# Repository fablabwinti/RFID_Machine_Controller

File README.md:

# RFID_Machine_Controller
This repository contains the hardware design files (eagle) and the firmware (Arduino) for the Fablab Winti RFID machine access controller. 
## Hardware features
- Based on ESP8266 so it has direct access to WiFi
- RFID reader 
- OLED display
- Piezo buzzer
- Multi-color LED
- SD card for event logging
- RTC for accurate time keeping without network access
- Isolated output with screw terminal
  - Option 1: Relay output: 250V, 5A, NC or NO with a 5x20mm fuse
  - Option 2: Opto-coupled output (50V, 40mA)
- Input voltage: 5V ±0.5V with input protection (reverse voltage protection, overvoltage protection)
- Three input connecters: 5.5x2.1mm DC jack, Micro USB jack, screw termianl

## Firmware features
- Easy web based configuration
- Time sync through NTP
- Automatic synchronization of local RTC 
- Automatic update of user database from server
- Local storage of access rights: works during network failures
- Local data logging to SD-Card or Flash (TBD)
- Transmit log data to server as soon as it is available

## Arduino IDE
### Add Board to IDE
File -> Preferences -> Settings -> Additional boards manager URLs: http://arduino.esp8266.com/stable/package_esp8266com_index.json  
### Install Board
Tools -> Boards -> Boards Manager
Search for "esp8266" and install it
### Select Board
Tools -> Boards -> esp8622 -> "Generic ESP8622 Module"
### Board Configurations
Select the following settings under "Tools"

### Install Libraries
Unzip "FabLabRFID_Library.zip" in the arduino library folder:

- Windows: `C:\Users\{username}\Documents\Arduino`
- macOS: `/Users/{username}/Documents/Arduino`
- Linux: `/home/{username}/Arduino`

#### Manually

Tools -> Manage Libraries

Install all libraries as described in Fablab_RFID_control.ino, line 52 to 70 (?)

MRFC522: Download from git (https://github.com/miguelbalboa/rfid) and add it to the library (.../Documents/Arduino/Libraries/...)

## Upload Flash Content

The `spiffs_flash.py` script automatically builds the SPIFFS filesystem image from the `data` directory and uploads it to the ESP8266.

### Prerequisites
- Python 3.x installed
- ESP8266 connected via USB
- Arduino15 directory present (auto-detected or manually specified)

### Usage

Basic upload (auto-detects Arduino15 directory):
```bash
python spiffs_flash.py --port COM8
```

With custom options:
```bash
# Specify Arduino15 directory manually
python spiffs_flash.py --port COM8 --arduino-root "C:\Users\YourName\AppData\Local\Arduino15"

# Erase SPIFFS region before writing (if write fails)
python spiffs_flash.py --port COM8 --erase-region

# Keep temporary build files for inspection
python spiffs_flash.py --port COM8 --keep-temp

# Use existing .bin file (skip build)
python spiffs_flash.py --port COM8 --bin path\to\existing.spiffs.bin
```

### Troubleshooting
- If Arduino15 not found, the script will prompt for the path
- Use `--erase-region` if you encounter write errors (preserves main firmware)
- Change COM port number to match your device (check Device Manager on Windows)

# License
-Firmware under GNU LGPL Version 3
-Hardware under Creative Commons 4.0 license: CC-BY-SA

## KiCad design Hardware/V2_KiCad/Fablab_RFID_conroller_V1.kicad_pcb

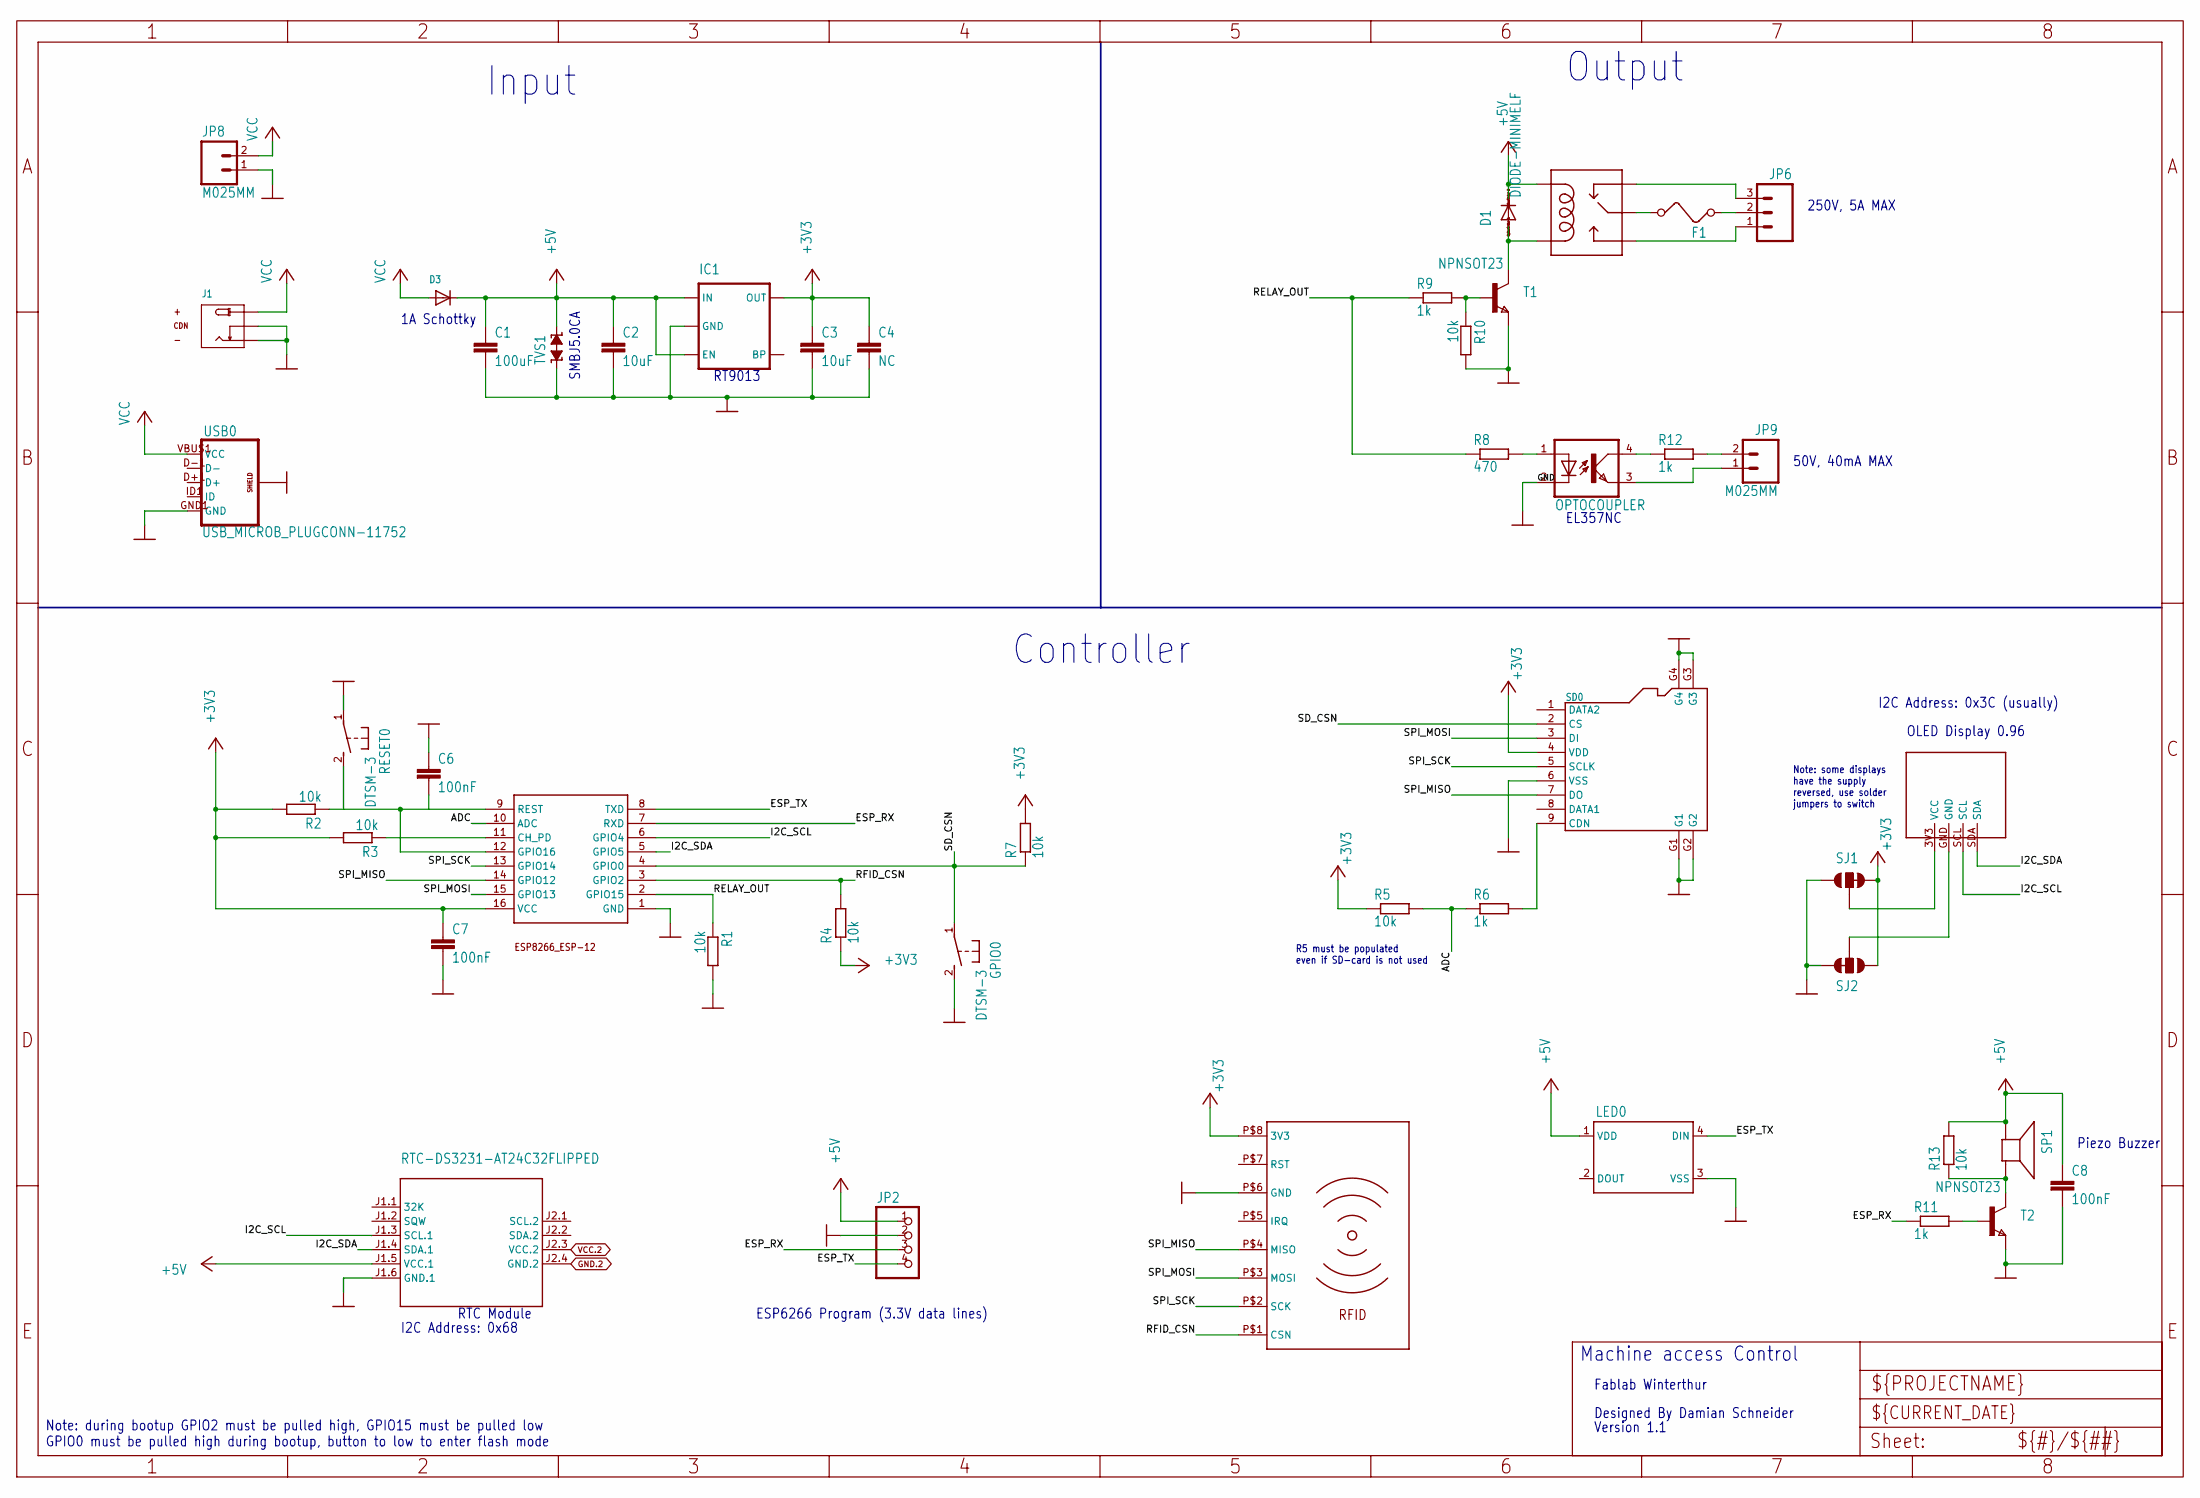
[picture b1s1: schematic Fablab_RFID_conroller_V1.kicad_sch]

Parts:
C1: 100uF; C1206
C2, C3: 10uF; C0805
C4: NC; C1206
C6, C7, C8: 100nF; C0603
D1: DIODE-MINIMELF; MINIMELF
D3: DIODESMA; SMADIODE
ESP0: ESP8266_ESP-12; ESP8266-ESP12
F1: FUSE
GPIO0: DTSM-3
IC1: V_REG_LDOSMD; SOT23-5
J1: JACK-DC-3P-3410020P1; PW-3P-2.1
JP2: HEADER-1X476MIL; 1X04_ROUND_76
JP6: M03-SCREW-5MM; SCREWTERMINAL-5MM-3
JP8, JP9: M025MM; SCREWTERMINAL-5MM-2
LED0: WS2812B
OC1: OPTOCOUPLER; SOP04
OLED0: OLED_0.96_I2CNOHOLES; OLED_0.96_I2C_NOHOLES
R1, R2, R3, R4, R5, R7, R10, R13: 10k; R0603
R6, R9, R11: 1k; R0603
R8: 470; R0603
R12: 1k; R0805
REL1: RELAYPTH; SRD-05VDC-SL-C
RESET0: DTSM-3
RFID0: RFID_MODULE_RC522; RFID-RC522-MODULE
SD0: MICRO-SDCARD-CONNECTOR-3300060P1; 9P-SMD-W-RING
SJ1, SJ2: JUMPER-PAD-3-2OF3_NC_BY_TRACE_LARGE; PAD-JUMPER-3-2OF3_NC_BY_TRACE_YES_SILK_LARGE
SP1: SPEAKER/AL60P; AL60P
T1, T2: NPNSOT23; SOT-23
TVS1: TVS-SMBJ; SMBJ
U$2: RTC-DS3231-AT24C32FLIPPED; RTC-DS3231_FLIPPED
USB0: USB_MICROB_PLUGCONN-11752; USB-B-MICRO-SMD_V03

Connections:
+3V3: C3.1, C4.1, C7.1, ESP0.16 (VCC), IC1.5 (OUT), R2.2, R3.2, R4.1, R5.1, R7.2, RFID0.P$8 (3V3), SD0.4 (VDD), SJ1.3, SJ2.1
+5V: C1.1, C2.1, C8.1, D1.C, D3.C, IC1.1 (IN), IC1.3 (EN), JP2.1, LED0.1 (VDD), R13.2, REL1.COIL1, SP1.1 (+), TVS1.C (2), U$2.J1.5 (VCC.1)
ADC: ESP0.10 (ADC), R5.2, R6.1
CHPD: ESP0.11 (CH_PD), R3.1
ESP_RX: ESP0.7 (RXD), JP2.3, R11.1
ESP_TX: ESP0.8 (TXD), JP2.4, LED0.4 (DIN)
GND: C1.2, C2.2, C3.2, C4.2, C6.1, C7.2, C8.2, ESP0.1 (GND), GPIO0.2, IC1.2 (GND), J1.-1 (-), J1.-2 (CDN), JP2.2, JP8.1, LED0.3 (VSS), OC1.2 (C), R1.2, R10.2, RESET0.1, RFID0.P$6 (GND), SD0.6 (VSS), SD0.G1, SD0.G2, SD0.G3, SD0.G4, SJ1.1, SJ2.3, T1.2 (E), T2.2 (E), TVS1.A (1), U$2.J1.6 (GND.1), USB0.GND1 (GND), USB0.SHIELD1 (SHIELD), USB0.SHIELD2 (SHIELD), USB0.SHIELD3 (SHIELD)
GND.2: U$2.J2.4 (GND.2)
I2C_SCL: ESP0.6 (GPIO4), OLED0.SCL, U$2.J1.3 (SCL.1)
I2C_SDA: ESP0.5 (GPIO5), OLED0.SDA, U$2.J1.4 (SDA.1)
unnamed: JP9.2, R12.2
unnamed: OLED0.3V3 (VCC), SJ1.2
unnamed: OLED0.GND, SJ2.2
unnamed: R9.2, R10.1, T1.3 (B)
unnamed: D1.A, REL1.COIL0, T1.1 (C)
unnamed: R13.1, SP1.2 (-), T2.1 (C)
unnamed: R11.2, T2.3 (B)
unnamed: F1.1, JP6.2
unnamed: JP6.1, REL1.SW_NO (SWOPEN)
unnamed: F1.2, REL1.SWCOMMON
unnamed: JP6.3, REL1.SW_NC (SWCLOSE)
unnamed: OC1.1 (A), R8.2
unnamed: OC1.4 (COL), R12.1
unnamed: JP9.1, OC1.3 (EMIT)
RELAY_OUT: ESP0.2 (GPIO15), R1.1, R8.1, R9.1
RESET: C6.2, ESP0.9 (REST), ESP0.12 (GPIO16), R2.1, RESET0.2
RFID_CSN: ESP0.3 (GPIO2), R4.2, RFID0.P$1 (CSN)
SD_CSN: ESP0.4 (GPIO0), GPIO0.1, R7.1, SD0.2 (CS)
SPI_MISO: ESP0.14 (GPIO12), RFID0.P$4 (MISO), SD0.7 (DO)
SPI_MOSI: ESP0.15 (GPIO13), RFID0.P$3 (MOSI), SD0.3 (DI)
SPI_SCK: ESP0.13 (GPIO14), RFID0.P$2 (SCK), SD0.5 (SCLK)
VCC: D3.A, J1.+, JP8.2, USB0.VBUS1 (VCC)
VCC.2: U$2.J2.3 (VCC.2)
~SDCARD_DETECT: R6.2, SD0.9 (CDN)

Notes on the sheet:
250V, 5A MAX
1A Schottky
RT9013
Piezo Buzzer
Note: during bootup GPIO2 must be pulled high, GPIO15 must be pulled low GPIO0 must be pulled high during bootup, button to low to enter flash mode
Machine access Control
EL357NC
Output
Fablab Winterthur
Input
RTC Module
Note: some displays have the supply reversed, use solder jumpers to switch
Version 1.1
I2C Address: 0x3C (usually)
SMBJ5.0CA
Controller
R5 must be populated even if SD-card is not used
50V, 40mA MAX
ESP6266 Program (3.3V data lines)
Designed By Damian Schneider
OLED Display 0.96
I2C Address: 0x68

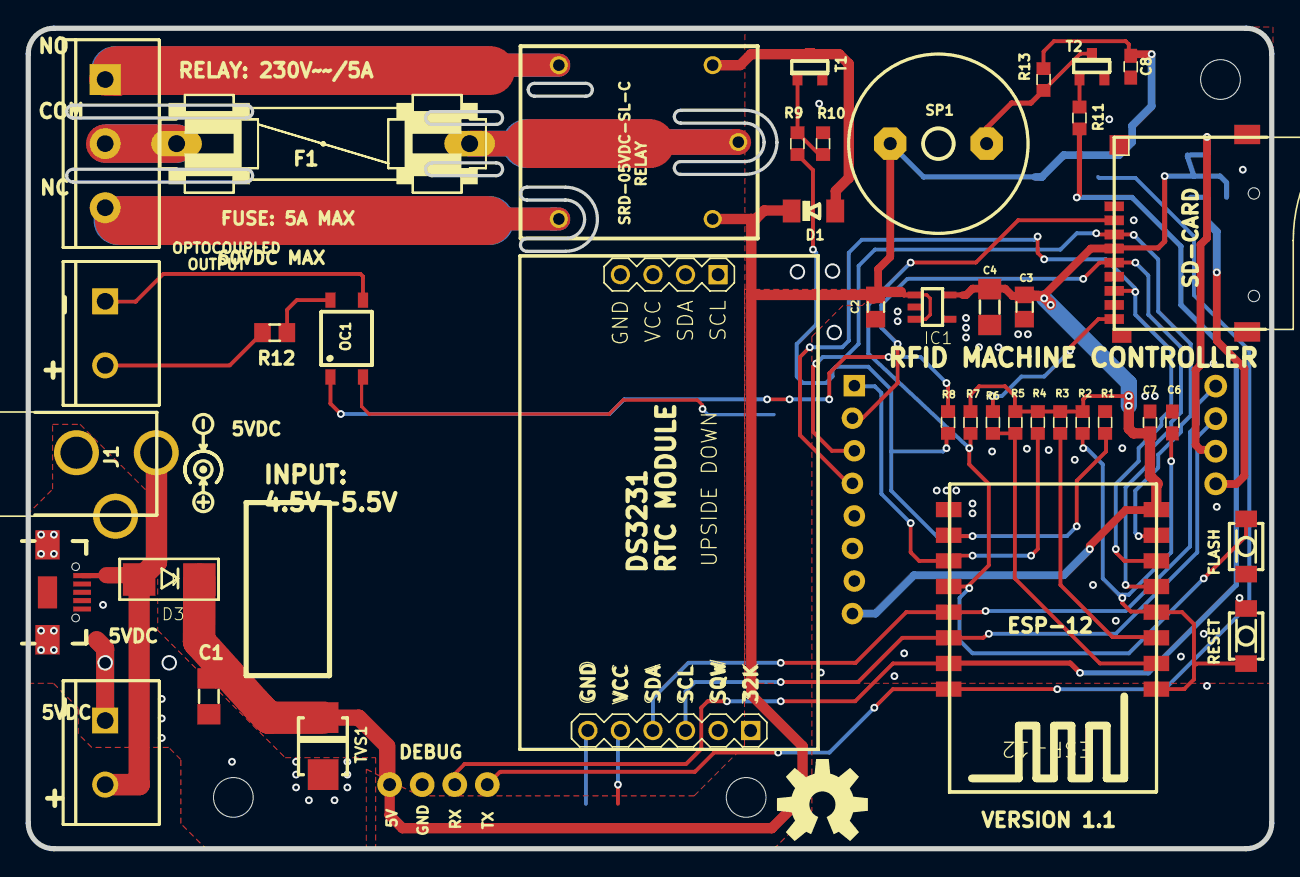
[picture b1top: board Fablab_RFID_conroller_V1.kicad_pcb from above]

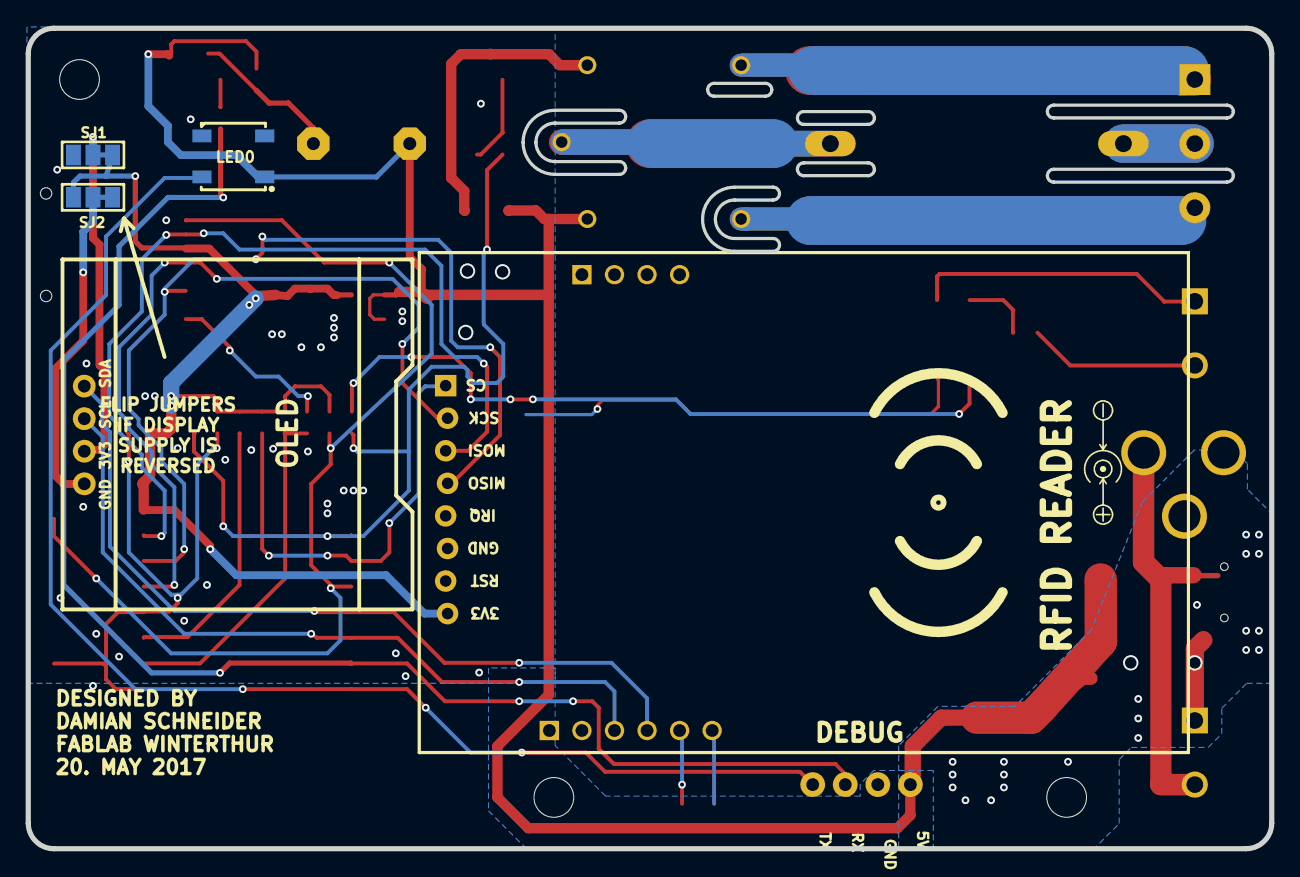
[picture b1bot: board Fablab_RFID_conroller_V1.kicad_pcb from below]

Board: 2 copper layers, 97.0 x 64.0 mm, 50 parts (5 on the bottom side), 32 nets.

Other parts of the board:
@HOLE0, @HOLE1, @HOLE2: (no value)
U$6: OSHW-LOGO-L

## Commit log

2017-06-03 updated readme with license
2017-06-03 Initial project commit
    PCB rev. 1 is done but not veryfied, license for hardware added
2017-06-03 license to markdown
2017-06-03 remove obsolete file
2017-06-04 add SD card to BOM
2017-06-04 initial firmware commit
    just basic functionality and lots of debugging messages, not really
    useable yet
2017-06-11 removed OTA support, changed LED behaviour
    OTA was replaced by secure web update
2017-06-11 removed watchdog timer
    it conflicts somehow with the fastled library. also the controller
    should never atuomatically reboot
2017-06-11 rename
2017-06-11 sound support for final version
    changed pin from debug to final, added login and logout sound, changed
    function names
2017-06-11 reorganized timer management
    RTC runs on epoch (UNIX) time, local clock runs on local time, including
    timezone and automatic DST (europe)
2017-06-11 add display support on init
2017-06-11 code rearranged
2017-06-11 big update on display support
    -adding logo
    -adding proper display during login/logout
    -added time on the display
2017-06-11 huge update
    -added functionality to properly login/logout
    -not accepting any cards while logged in except the user who logged in
    -improved user handling
2017-06-11 led support and global variable added
2017-06-11 remove OTA
2017-06-11 changed to fastled library, code cleanup
2017-06-11 update on used libraries and code cleanup
    also adding display support during bootup
2017-08-15 Major update: local database now loaded from server
    -added server connectivity (working)
    -updated local user database to match server (working)
    -added display name from database
    -preliminary implemenation of SD card database for events
    -added event handling (incomplete)
    -added JSON library for endoding and decoding
2017-08-17 added event generation functions
    and debugged SD card database saving, now fully working
    also added proper timestamp string generation
    plus some small bugfixes
2017-08-20 started updating config stuff, started on RFID advanced auth
    -added handling of more eeprom config variables
    -added support to make all config page traffic websocket based (webpage
    still needs updating)
    -changed server sendouts to use data from config (no more fixed strings)
    -added password support for config page access
    -cleaned up the todo list
2017-08-22 Bugfixes & Working on Config Webpage
    trying to get the config page up to speed, partially working but still
    work in progress
2017-08-24 finished direct database request of machine names
    MID and MNAME are added to the option select menu, a manual menu is
    shown if connection fails.
2017-08-26 big config page update
    -fixed some bugs on webpage and in firmware
    -added config support
    -website now downloads machine list from server automatically
    -changed ajax loader.gif
    -added firmware and spiffs image file update directly from the server
    (triggered on config page)
2017-08-26 updated schematic with errata
2017-08-26 removed update server
    it is no longer needed thanks to http update
2017-09-08 bugfixes & cosmetics
2017-12-30 RFID and config Update
    - added framework for RFID authentication using the access key and a
    passphrase saved on the card, configurable on the webpage
    -Added a few variables to the config
    -Made web page credentials configurable
    -Prepared for the use of an API key, it can be entered on the webpage
    -changed factory reset: can now be done before any code runs, as a
2018-01-21 updated for new server version
    -changed api URI to /api/...
    -changed event number definitions
    -added error logs
    -added logs for unsuccessful tag access
    -updated BOM
    -added tag time verification
2018-01-21 display layout update
    fonts added, some useful, some not
2018-01-23 bugfix: writing to nonexisting SD card no more
2018-01-25 added status icons
    also added som additional compiling info, it now works on arduino 1.8.5
    with ESP version 2.4.0 (which it did not before, not sure what change
    made that possible)
    Status icons is work in progress.
2018-07-16 Add missing global variable.
2018-07-16 Add hand-drawn fonts and replace all use of other small fonts by them.
2018-07-16 Fix status icons.
    The previous ones only displayed pixel garbage for me.
2018-07-16 Add checkmark/cross icons to transition screens.
2018-08-12 refactoring & minor fixes
    forgot to commit for a long time... only minor code changes
2018-08-12 fixed errors after merging pull request
    also made server connection timeout shorter to avoid long delays in
    login if server is not available
2018-11-25 minor bugfixes
    -added login/logout function of admin tag also during a websocket
    session
2019-04-29 stability update and added post logout switch delay
    disabling wifi during login times to increase stability (hopefully). had
    to add a delay before disabling wifi or it would crash very often...
    also some minor bugfixes here and there.
2019-05-01 stability improvement added post logout user data display
    disabled software watchdog,
    improved sendout/sd saving handling
    after logout, time is still displayed for 10 sec
    no more crashes (so far) when disabling wifi
2019-05-12 major update, added fatfs, added new way of secure connection, added more machine options
    plus some code cleanup, stability improvement yet again, added log to SD
    card every time interval. still need to do price calculation but
    everything is prepared for that.
2019-05-12 changed to normal EDB again, fork was fully code compatible
2019-05-12 updated SD stuff
2019-05-15 added price calculation
2019-06-22 updated event database, added key read from spiffs
    -event database is now also in spiffs, can be put on SD card by changing
    a define
    -public key (pem) is read from file in spiffs so it can be configured in
    real time (not yet implemented)
2020-02-04 added ssh file handling with public key
    upload may not yet work through webpage but works through direct spiffs
    upload
2020-02-23 update for arduinojson v 6.x
    updated to use new version of arduinojson
2020-02-25 update serial
2020-02-25 add fablab pem key file
2020-02-28 bugfix in json parsing
2020-02-29 typo
2020-03-07 LED update bugfix, Serial debug output refactor
2023-12-26 Fix use of uninitialized variable.
    It could randomly cause logs to be sent to the server without a tid.
2023-12-26 Send log events to the server in the order they were created.
    The previous partly-reversed order made it hard to interpret them on the server when timestamps were not chronological due to network time updates or RTC failure.
    The database in SPIFFS and the queue in RAM, in that order, now form a combined FIFO queue. Entries are sent to the server directly from the RAM queue if possible, but if not, moved to the flash data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
2023-12-28 Fix failing database update with 4 or more user entries.
    Trying to parse up to 5 entries at once did not work, it already ran into a NoMemory error at 4 fully specified entries with the 512 byte document buffer. Parse them one by one instead, following htt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
2024-05-09 Address erratum: Fix +5V connection of relay coil.
2024-05-09 Address erratum: Replace diode D2 by 10k resistor R13.
2024-05-09 Regenerate PDF and Gerber files for version 1.1.
2024-10-22 Observe the minimum periods price for the cost display.
    Adjust to the current server that provides this field in the machine database.
    The additional configuration field requires introducing versioning in the EEPROM data structure.
2024-11-19 Remove unused files.
2025-11-12 KiCad transfer
    New KiCad Project, contains old Eagle Project (not tested yet)
2025-11-24 Update library version comments to the ones that work for me.
2025-11-24 added library files + spiffs_flash.py
2026-04-30 docs: add Docs/ folder and AiTasks with current firmware documentation
